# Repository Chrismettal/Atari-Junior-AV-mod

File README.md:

# Atari 2600 Junior composite AV mod <!-- omit in toc -->

This is a single board solution to mod Atari 2600 Junior consoles, which normally only use RF outputs, into outputting composite AV.

Analog RF isn't typically found on most modern TVs anymore, and even composite AV is fading out, but it is still fairly easy to hook up on most systems.

This mod in general isn't anything new, it has been for literal decades but usually it was done with free floating wires and components. This PCB aims to make installation a lot easier.

All files to manufacture your own boards are uploaded in the [production files directory](/pcb/production%20files/), but for your convenience, finished boards are also stocked at [Tindie](https://www.tindie.com/products/binary-6/2600-junior-composite-av-mod-atari/).

**If you like my work please consider [supporting my caffeine addiction](https://github.com/Chrismettal#donations)!**

## Table of contents <!-- omit in toc -->

- [Compatibility](#compatibility)
- [Installation](#installation)
  - [Stuff required](#stuff-required)
  - [Opening the console](#opening-the-console)
  - [Placing the mod](#placing-the-mod)
  - [Choosing between PAL and NTSC](#choosing-between-pal-and-ntsc)
  - [Wiring it up](#wiring-it-up)
- [Making your own](#making-your-own)
- [Ancient version](#ancient-version)
- [Sources](#sources)
- [Used tools](#used-tools)
- [License](#license)

## Compatibility

This mod is compatible to PAL and NTSC versions, configurable via jumpers.

Please make sure your Junior board mechanically looks like the one shown in the installation guide below. There are some revisions, namely **Rev D boards**, that are mechanically different in the lower left corner where the mod is supposed to be placed, that prevent the PCB from slotting in.

## Installation

This installation guide was done on a **PAL Rev C Junior board**.

### Stuff required

- AV Modchip
- Audio / Video ports of your liking (RCA for example)
- Screened wire (Stereo audio cable works well)
- Soldering iron
- Screwdrivers / Pliers
- 30 Minutes of time

### Opening the console

The case gets flipped on its face and 5 screws will be removed. On the front you
will find some clips that need to be carefully opened as well. The old plastic likes
to break easily.

The metal panel has multiple bent tabs around the perimiter that need to be bent
straight again to take the panel off.

### Placing the mod

In the lower left hand corner there is the backside of the CD4050 IC. Place the modchip according to the picture. It will fit over all pins in
the area. There are 7 contacted holes that need to be soldered in. This will
connect all video as well as audio signals to the modboard. Sometimes you are required to bend some pins up with a screwdriver if the chip does not fit perfectly.

### Choosing between PAL and NTSC

You will need to set **JP1** and **JP2** according to your system. Both jumpers need to be connected **MIDDLE-DOWN** (1-2) for PAL systems, or **MIDDLE-UP** (2-1) for NTSC systems.

If you fail to connect any jumpers, you will not get any usable video out of your system, but nothing will break.

In this guide, Both jumpers were set **MIDDLE-DOWN** since I am using a PAL system.

### Wiring it up

The top left corner of the chip has contacts for audio and video, in my case:

- Screening – GND
- Red – Audio
- White – Video

I wired up a triple RCA jack here, putting the audio signal on both center pins of
the red and white jack for left and right audio, the video signal onto the center
pin of the yellow jack, and GND on the outer ring of all three

After routing the wires you can put the screening panel back on and bend the
metal tabs back into place

This is what the ports could look like. Of course you don’t have to put the jacks as
crooked as I did.

## Making your own

All files to manufacture your own boards are uploaded in the [production files directory](/pcb/production%20files), but for your convenience, finished boards are also stocked at [Tindie](https://www.tindie.com/products/binary-6/2600-junior-composite-av-mod-atari/).

The production files were created with [JLCPCB](https://jlcpcb.com) in mind. The BOM and Gerbers specifically fit their requirements to have the full PCB panel including PCBA assembly manufactured with them. Alternatively, in the [BOM](/pcb/production%20files/bom/atari-junior-av-mod.csv) you will find LCSC part numbers to buy the parts at [LCSC](https://lcsc.com) individually.

## Ancient version

The initial version was never published open source, but has been added here for legacy documentation purposes. 

It was originally done in EAGLE but imported into KiCad. No fabrication files are provided and the files are not imported perfectly. The manual still references this version of the board, as the general installation procedure did not really change. 

The old version was only compatible to PAL systems, while the new board released here also works on NTSC systems, as long as your Atari junior board revision fits mechanically.

## Sources

- Differences between PAL and NTSC PCBs by were documented in [AtariAge forums](https://atariage.com/forums/topic/309021-atari-2600-ntsc-simple-diy-composite-mod/).
- Ancient version was first published and documented in [CircuitBoard forums](https://circuit-board.de/forum/index.php/Thread/22430-Atari-2600-Junior-AV-Mod-mit-neuer-PCB/), referencing an original tutorial [in the same forum](https://circuit-board.de/forum/index.php/Thread/1886-Atari-2600-Junior-Video-Mod-ohne-Zusatzplatine/).

## Used tools

- [KiCAD Version 6.0.2](https://www.kicad.org/)

## License

<br />This work is licensed under a <a rel="license" href="http://creativecommons.org/licenses/by-nc-sa/4.0/">Creative Commons Attribution-NonCommercial-ShareAlike 4.0 International License</a>.

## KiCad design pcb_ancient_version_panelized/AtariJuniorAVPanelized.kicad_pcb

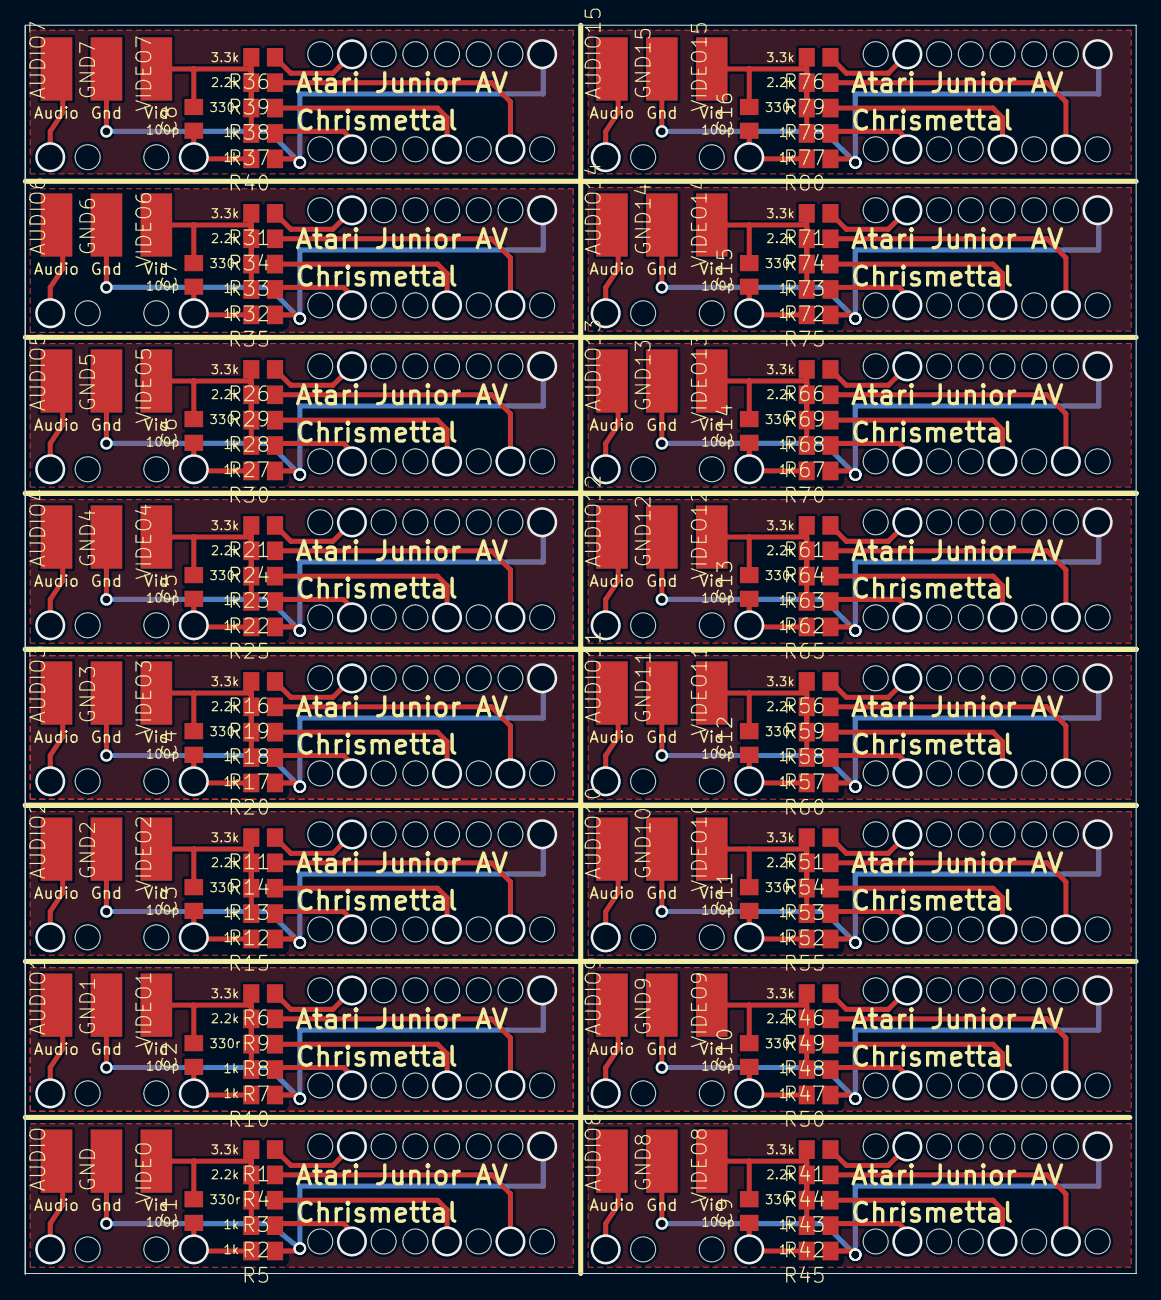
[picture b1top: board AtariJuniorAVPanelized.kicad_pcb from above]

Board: 16 copper layers, 89.0 x 100.1 mm, 352 parts (0 on the bottom side), 32 nets.

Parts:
@HOLE0, @HOLE1, @HOLE2, @HOLE3, @HOLE4, @HOLE5, @HOLE6, @HOLE7, @HOLE8, @HOLE9, @HOLE10, @HOLE11, @HOLE12, @HOLE13, @HOLE14, @HOLE15, @HOLE16, @HOLE17, @HOLE18, @HOLE19, @HOLE20, @HOLE21, @HOLE22, @HOLE23, @HOLE24, @HOLE25, @HOLE26, @HOLE27, @HOLE28, @HOLE29, @HOLE30, @HOLE31, @HOLE32, @HOLE33, @HOLE34, @HOLE35, @HOLE36, @HOLE37, @HOLE38, @HOLE39, @HOLE40, @HOLE41, @HOLE42, @HOLE43, @HOLE44, @HOLE45, @HOLE46, @HOLE47, @HOLE48, @HOLE49, @HOLE50, @HOLE51, @HOLE52, @HOLE53, @HOLE54, @HOLE55, @HOLE56, @HOLE57, @HOLE58, @HOLE59, @HOLE60, @HOLE61, @HOLE62, @HOLE63, @HOLE64, @HOLE65, @HOLE66, @HOLE67, @HOLE68, @HOLE69, @HOLE70, @HOLE71, @HOLE72, @HOLE73, @HOLE74, @HOLE75, @HOLE76, @HOLE77, @HOLE78, @HOLE79, @HOLE80, @HOLE81, @HOLE82, @HOLE83, @HOLE84, @HOLE85, @HOLE86, @HOLE87, @HOLE88, @HOLE89, @HOLE90, @HOLE91, @HOLE92, @HOLE93, @HOLE94, @HOLE95, @HOLE96, @HOLE97, @HOLE98, @HOLE99, @HOLE100, @HOLE101, @HOLE102, @HOLE103, @HOLE104, @HOLE105, @HOLE106, @HOLE107, @HOLE108, @HOLE109, @HOLE110, @HOLE111, @HOLE112, @HOLE113, @HOLE114, @HOLE115, @HOLE116, @HOLE117, @HOLE118, @HOLE119, @HOLE120, @HOLE121, @HOLE122, @HOLE123, @HOLE124, @HOLE125, @HOLE126, @HOLE127, @HOLE128, @HOLE129, @HOLE130, @HOLE131, @HOLE132, @HOLE133, @HOLE134, @HOLE135, @HOLE136, @HOLE137, @HOLE138, @HOLE139, @HOLE140, @HOLE141, @HOLE142, @HOLE143, @HOLE144, @HOLE145, @HOLE146, @HOLE147, @HOLE148, @HOLE149, @HOLE150, @HOLE151, @HOLE152, @HOLE153, @HOLE154, @HOLE155, @HOLE156, @HOLE157, @HOLE158, @HOLE159, @HOLE160, @HOLE161, @HOLE162, @HOLE163, @HOLE164, @HOLE165, @HOLE166, @HOLE167, @HOLE168, @HOLE169, @HOLE170, @HOLE171, @HOLE172, @HOLE173, @HOLE174, @HOLE175, @HOLE176, @HOLE177, @HOLE178, @HOLE179, @HOLE180, @HOLE181, @HOLE182, @HOLE183, @HOLE184, @HOLE185, @HOLE186, @HOLE187, @HOLE188, @HOLE189, @HOLE190, @HOLE191, @HOLE192, @HOLE193, @HOLE194, @HOLE195, @HOLE196, @HOLE197, @HOLE198, @HOLE199, @HOLE200, @HOLE201, @HOLE202, @HOLE203, @HOLE204, @HOLE205, @HOLE206, @HOLE207: (no value)
AUDIO, AUDIO1, AUDIO2, AUDIO3, AUDIO4, AUDIO5, AUDIO6, AUDIO7, AUDIO8, AUDIO9, AUDIO10, AUDIO11, AUDIO12, AUDIO13, AUDIO14, AUDIO15: WIREPADSMD2,54-5,08; SMD2,54-5,08
C1, C2, C3, C4, C5, C6, C7, C8, C9, C10, C11, C12, C13, C14, C15, C16: 100pF; C0805
GND, GND1, GND2, GND3, GND4, GND5, GND6, GND7, GND8, GND9, GND10, GND11, GND12, GND13, GND14, GND15: WIREPADSMD2,54-5,08; SMD2,54-5,08
R1, R6, R11, R16, R21, R26, R31, R36, R41, R46, R51, R56, R61, R66, R71, R76: 3.3k; R0805
R2, R5, R7, R10, R12, R15, R17, R20, R22, R25, R27, R30, R32, R35, R37, R40, R42, R45, R47, R50, R52, R55, R57, R60, R62, R65, R67, R70, R72, R75, R77, R80: 1k; R0805
R3, R8, R13, R18, R23, R28, R33, R38, R43, R48, R53, R58, R63, R68, R73, R78: 330r; R0805
R4, R9, R14, R19, R24, R29, R34, R39, R44, R49, R54, R59, R64, R69, R74, R79: 2.2k; R0805
VIDEO, VIDEO1, VIDEO2, VIDEO3, VIDEO4, VIDEO5, VIDEO6, VIDEO7, VIDEO8, VIDEO9, VIDEO10, VIDEO11, VIDEO12, VIDEO13, VIDEO14, VIDEO15: WIREPADSMD2,54-5,08; SMD2,54-5,08

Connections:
COLORIN: C1.1, R5.2
COLORIN1: C2.1, R10.2
COLORIN2: C3.1, R15.2
COLORIN3: C4.1, R20.2
COLORIN4: C5.1, R25.2
COLORIN5: C6.1, R30.2
COLORIN6: C7.1, R35.2
COLORIN7: C8.1, R40.2
COLORIN8: C9.1, R45.2
COLORIN9: C10.1, R50.2
COLORIN10: C11.1, R55.2
COLORIN11: C12.1, R60.2
COLORIN12: C13.1, R65.2
COLORIN13: C14.1, R70.2
COLORIN14: C15.1, R75.2
COLORIN15: C16.1, R80.2
unnamed: C1.2, R1.2, R2.2, R3.2, R4.2, VIDEO.1
unnamed: C2.2, R6.2, R7.2, R8.2, R9.2, VIDEO1.1
unnamed: C3.2, R11.2, R12.2, R13.2, R14.2, VIDEO2.1
unnamed: C4.2, R16.2, R17.2, R18.2, R19.2, VIDEO3.1
unnamed: C5.2, R21.2, R22.2, R23.2, R24.2, VIDEO4.1
unnamed: C6.2, R26.2, R27.2, R28.2, R29.2, VIDEO5.1
unnamed: C7.2, R31.2, R32.2, R33.2, R34.2, VIDEO6.1
unnamed: C8.2, R36.2, R37.2, R38.2, R39.2, VIDEO7.1
unnamed: C9.2, R41.2, R42.2, R43.2, R44.2, VIDEO8.1
unnamed: C10.2, R46.2, R47.2, R48.2, R49.2, VIDEO9.1
unnamed: C11.2, R51.2, R52.2, R53.2, R54.2, VIDEO10.1
unnamed: C12.2, R56.2, R57.2, R58.2, R59.2, VIDEO11.1
unnamed: C13.2, R61.2, R62.2, R63.2, R64.2, VIDEO12.1
unnamed: C14.2, R66.2, R67.2, R68.2, R69.2, VIDEO13.1
unnamed: C15.2, R71.2, R72.2, R73.2, R74.2, VIDEO14.1
unnamed: C16.2, R76.2, R77.2, R78.2, R79.2, VIDEO15.1

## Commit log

2022-01-04 Add repo structure
2022-01-04 Add .gitignore
2022-01-04 Update KiCAD ignores
2022-01-04 Add import of ancient PCB version
2022-01-04 Add empty project for new PCB
2022-01-04 idk ancient version doing a weird
2022-01-04 Start setting up KiCAD project
2022-01-05 Start creating schematic
2022-01-23 Add pictures of ancient version
2022-01-23 Add ancient panelized version
2022-01-23 Remove non-panelized ancient version and document panelized one
2022-01-23 Add some sources to README
2022-01-23 Add "#auto_saved_files#" to .gitignore
2022-01-23 Beautify schematic and add mechanical footprints
2022-01-23 Beautfy schematic
2022-01-23 Align mechanical components
2022-01-23 Finish most mechanical design
2022-01-23 Silkscreen
2022-01-26 Move stuff around a bit and add more silkscreen
2022-01-26 Generate 3d files for single version
2022-01-26 Export schematic
2022-01-26 Start panelizing
2022-01-26 Panelize
2022-01-26 Add git version hash
2022-01-26 Unify coordinate systems
2022-01-26 Update BOM
2022-01-26 Export production files to be ordered
2022-01-26 idk tbh
2022-02-15 Update license
2022-02-20 Update documentation for release
2022-02-20 Add compatibility information to readme
2022-02-20 Remove CHANGELOG.md and add used tools to readme
2022-04-21 Update Logo _ --> -
2022-04-21 Export 043c1d1 gerbers
2023-05-01 Remove Kofi
